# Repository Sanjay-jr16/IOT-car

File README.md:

# IOT-car
On-board diagnostics (OBD) is an automotive term referring to a vehicle's self-diagnostic and reporting capability. Up till now, OBD has evolved to OBD-II standard with 16 pins interface. 5 signaling protocols are permitted in the OBD-II interface, being SAE J1850 PWM, SAE J1850 VPW, ISO 9141-2, ISO 14230 KWP2000, and ISO 15765 CAN. To simply the design, this PCB only supports Controller Area Network (CAN) protocol.

The communication between an Arduino board and a vehicle is realized by two chips. MCP2551 is used as the interface between a CAN physical layer and a CAN protocol controller. STN1110 is a multiprotocol OBD to UART interpreter that supports all 5 protocols. Here we only use its CAN protocol translation functionality. The schematics of the connection is shown in the attachment.

Though both chip datasheets provide sample circuit schematics, It is worth noting that selection of the capacitors for the crystal is critical. Differential crystal may have different cap loading. Selecting wrong cap values will result in different oscillation frequency, and thus the communication between STN1110 and MCP2551 will fail. Adafruit has a good tutorial of how to calculate the value of the capacitors that attach to the crystal. A general rule of thumb is C1, C2 = 2*CL - 2*Cstray, where CL is the crystal's load capacitance, Cstray is the parasitic capacitance and is approximately 2-5 pF.

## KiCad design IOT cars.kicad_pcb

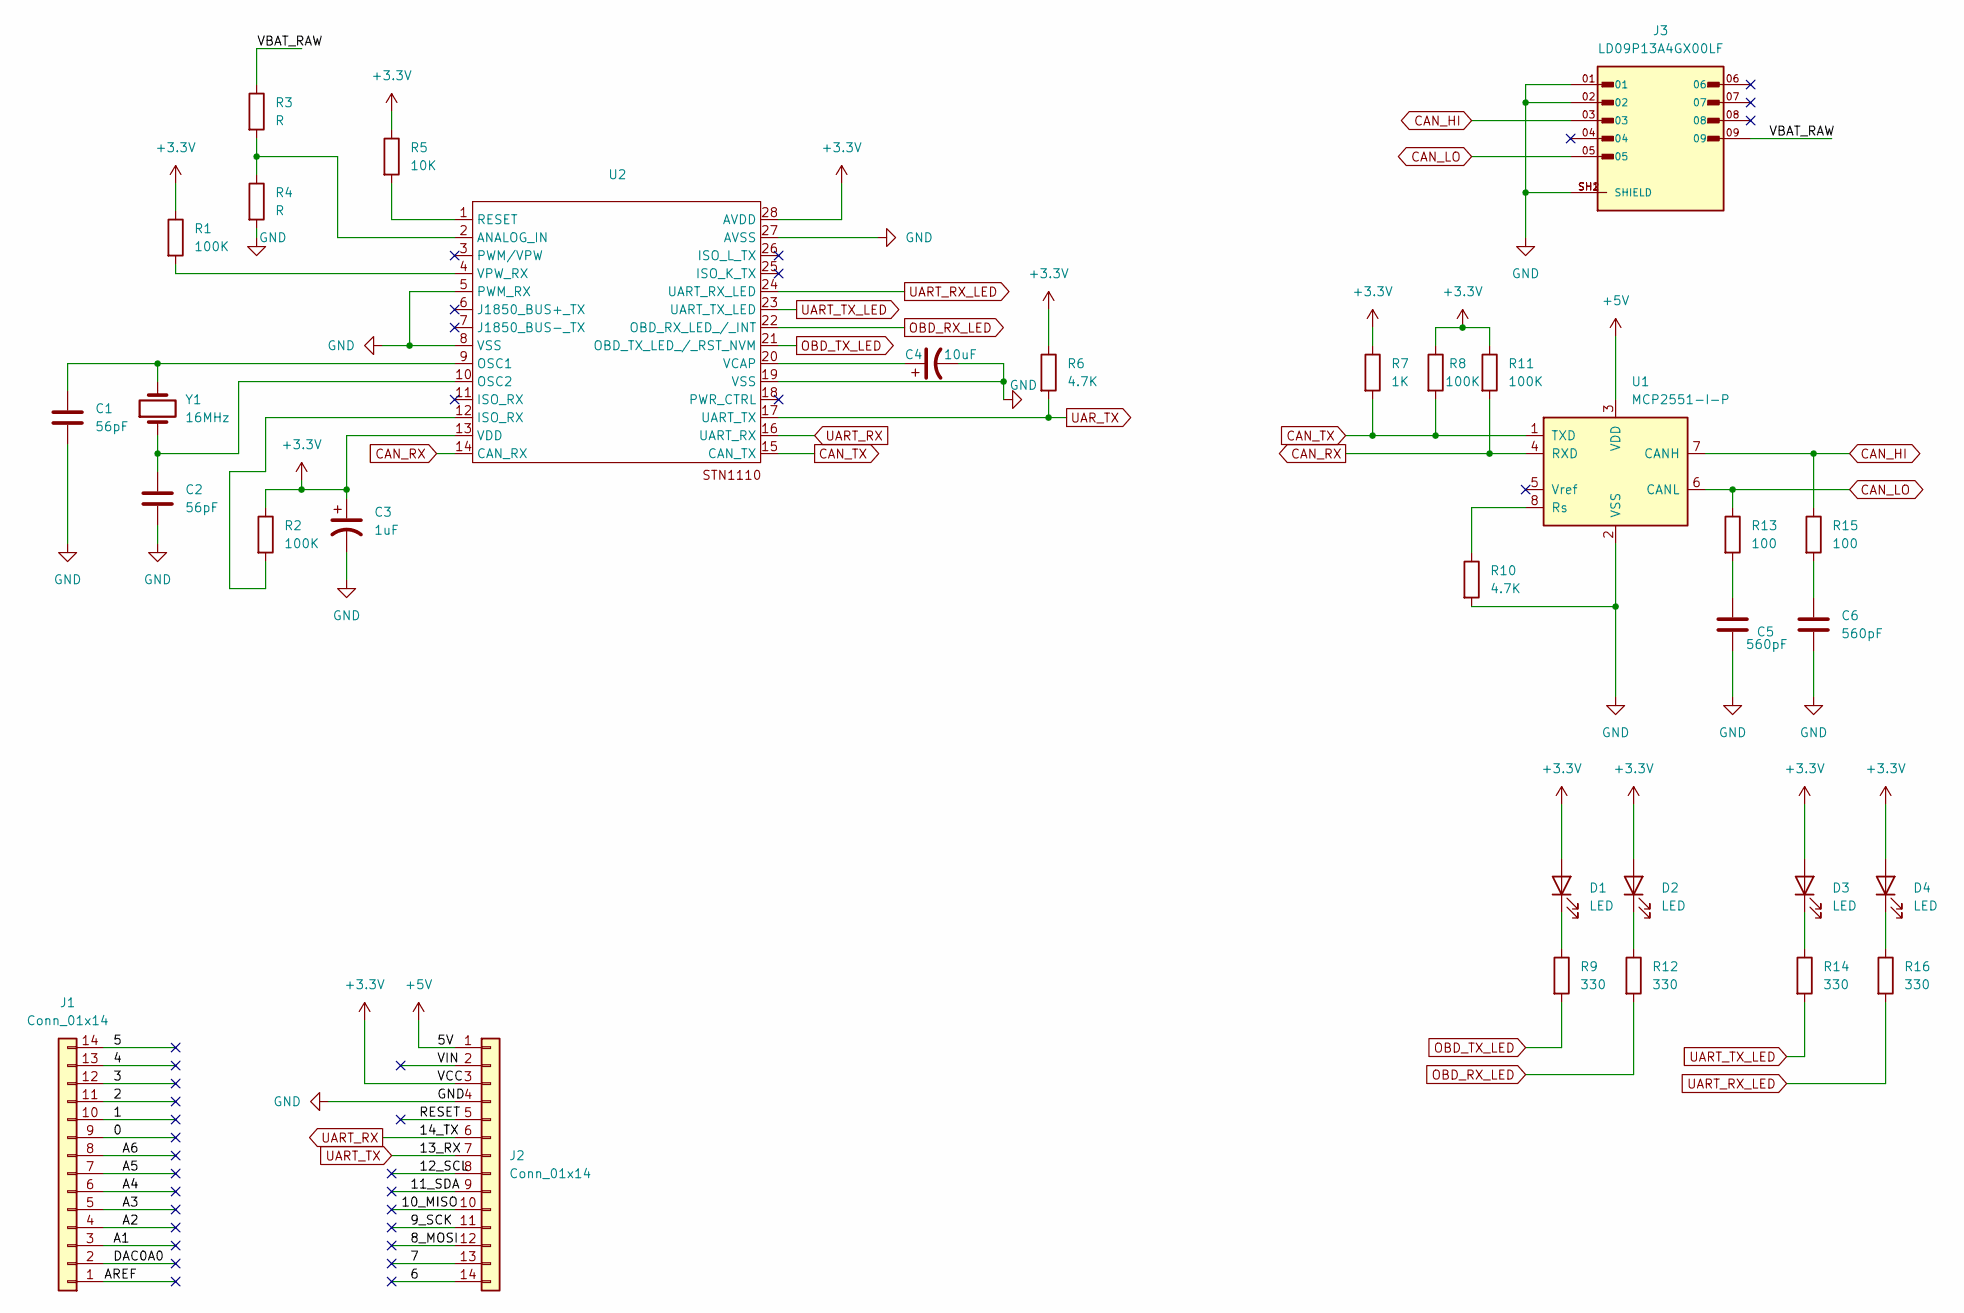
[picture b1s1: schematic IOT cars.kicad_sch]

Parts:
C1, C2: 56pF; C_Disc_D10.5mm_W5.0mm_P7.50mm
C3: 1uF; CP_Radial_D6.3mm_P2.50mm
C4: 10uF; CP_Radial_D5.0mm_P2.50mm
C5, C6: 560pF; C_Disc_D3.0mm_W2.0mm_P2.50mm
D1, D2, D3, D4: LED; LED_D5.0mm
J1, J2: Conn_01x14; PinSocket_1x14_P1.00mm_Vertical
J3: LD09P13A4GX00LF; TE_1-84952-0_1x10-1MP_P1.0mm_Horizontal; PARTREV B; DigiKey_Part_Number 609-5183-ND
R1, R2, R8, R11: 100K; R_Axial_DIN0411_L9.9mm_D3.6mm_P20.32mm_Horizontal
R3, R4: R; R_Axial_DIN0207_L6.3mm_D2.5mm_P15.24mm_Horizontal
R5: 10K; R_Axial_DIN0614_L14.3mm_D5.7mm_P15.24mm_Horizontal
R6, R10: 4.7K; R_Axial_DIN0207_L6.3mm_D2.5mm_P7.62mm_Horizontal
R7: 1K; R_Axial_DIN0207_L6.3mm_D2.5mm_P7.62mm_Horizontal
R9, R12, R14, R16: 330; R_Axial_DIN0207_L6.3mm_D2.5mm_P7.62mm_Horizontal
R13, R15: 100; R_Axial_DIN0207_L6.3mm_D2.5mm_P7.62mm_Horizontal
U1: MCP2551-I-P; DIP-8_W7.62mm
U2: Untitled
Y1: 16MHz; Crystal_HC49-4H_Vertical

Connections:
+3.3V: C3.1, D1.2 (A), D2.2 (A), D3.2 (A), D4.2 (A), J2.3, R1.1, R2.1, R5.1, R6.1, R7.1, R8.1, R11.1, U2.13 (VDD), U2.28 (AVDD)
+5V: J2.1, U1.3 (VDD)
/0: J1.9
/1: J1.10
/2: J1.11
/3: J1.12
/4: J1.13
/5: J1.14
/6: J2.14
/7: J2.13
/8_MOSI: J2.12
/9_SCK: J2.11
/10_MISO: J2.10
/11_SDA: J2.9
/12_SCL: J2.8
/ A1: J1.3
/ AREF: J1.1
/A2: J1.4
/A3: J1.5
/A4: J1.6
/A5: J1.7
/A6: J1.8
/DAC0A0: J1.2
/RESET: J2.5
/VBAT_RAW: J3.09, R3.1
/VIN: J2.2
CAN_HI: J3.03, R15.1, U1.7 (CANH)
CAN_LO: J3.05, R13.1, U1.6 (CANL)
CAN_RX: R11.2, U1.4 (RXD), U2.14 (CAN_RX)
CAN_TX: R7.2, R8.2, U1.1 (TXD), U2.15 (CAN_TX)
GND: C1.2, C2.2, C3.2, C4.2, C5.2, C6.2, J2.4, J3.01, J3.02, J3.SH1 (SHIELD), J3.SH2 (SHIELD), R4.2, R10.2, U1.2 (VSS), U2.5 (PWM_RX), U2.8 (VSS), U2.19 (VSS), U2.27 (AVSS)
unnamed: C5.1, R13.2
unnamed: C6.1, R15.2
unnamed: D1.1 (K), R9.1
unnamed: D2.1 (K), R12.1
unnamed: D3.1 (K), R14.1
unnamed: D4.1 (K), R16.1
unnamed: R2.2, U2.12 (ISO_RX)
unnamed: R10.1, U1.8 (Rs)
unnamed: R3.2, R4.1, U2.2 (ANALOG_IN)
unnamed: C1.1, U2.9 (OSC1), Y1.2
unnamed: C2.1, U2.10 (OSC2), Y1.1
unnamed: R5.2, U2.1 (RESET)
unnamed: C4.1, U2.20 (VCAP)
unnamed: R1.2, U2.4 (VPW_RX)
OBD_RX_LED: R12.2, U2.22 (OBD_RX_LED_/_INT)
OBD_TX_LED: R9.2, U2.21 (OBD_TX_LED_/_RST_NVM)
UART_RX: J2.6, U2.16 (UART_RX)
UART_RX_LED: R16.2, U2.24 (UART_RX_LED)
UART_TX: J2.7
UART_TX_LED: R14.2, U2.23 (UART_TX_LED)
UAR_TX: R6.2, U2.17 (UART_TX)

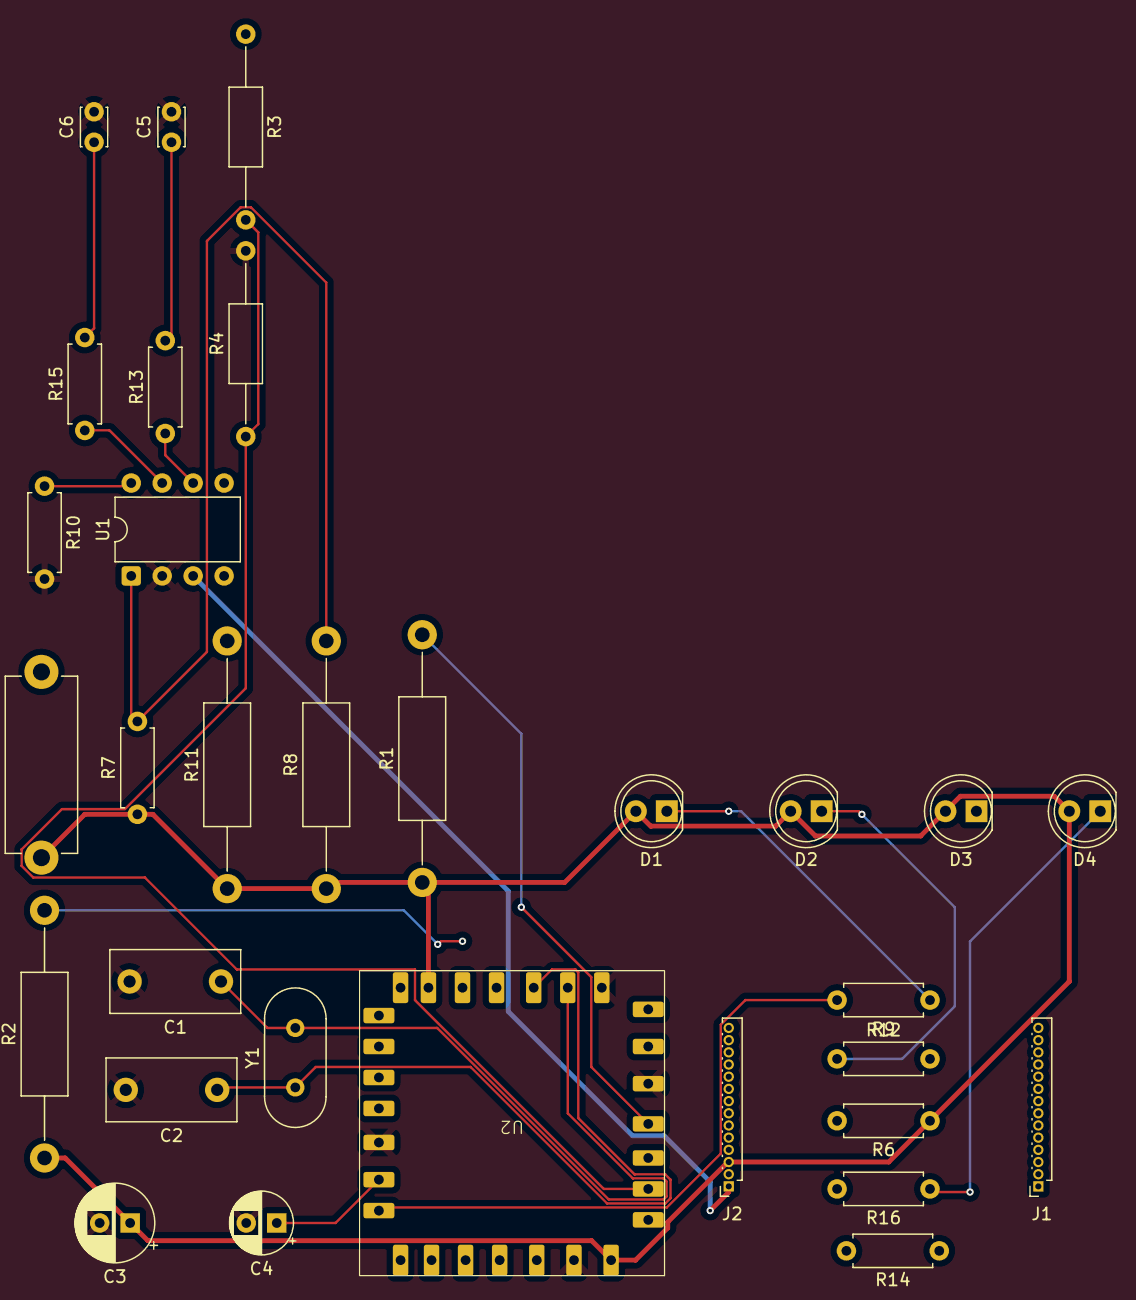
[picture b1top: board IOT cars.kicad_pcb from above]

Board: 4 copper layers, 31 parts (0 on the bottom side), 27 nets.

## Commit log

2025-07-22 Schematic Daigram
2025-07-22 Gerber files
